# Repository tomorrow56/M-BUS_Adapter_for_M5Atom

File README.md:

# M-BUS_Adapter_for_M5Atom

### Support Page
https://thousandiy.wordpress.com/2020/05/22/m5atom-to-m-bus-adapter/

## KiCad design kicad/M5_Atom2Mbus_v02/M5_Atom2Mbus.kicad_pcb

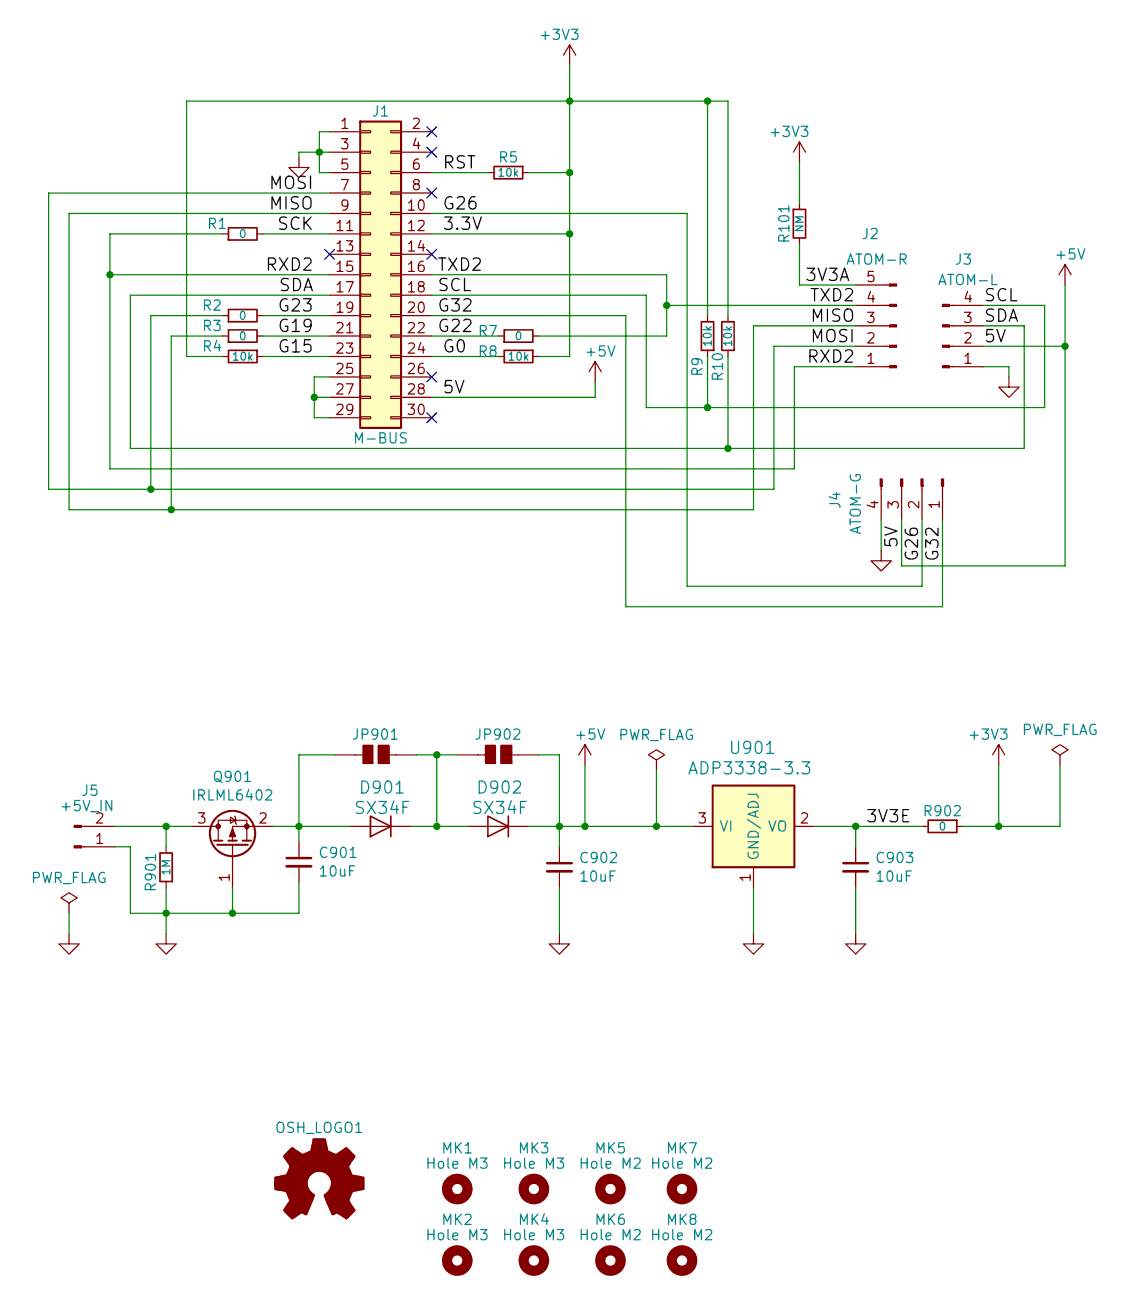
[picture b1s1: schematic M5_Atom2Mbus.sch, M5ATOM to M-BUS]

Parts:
C901, C902, C903: 10uF; C_0603_1608Metric
D901, D902: SX34F; D_SMA
J1: M-BUS; Pin_Header_MBUS_SMD_TH
J2: ATOM-R; PinHeader_1x05_P2.54mm_Vertical
J3: ATOM-L; PinHeader_1x04_P2.54mm_Vertical
J4: ATOM-G; Grove_4x2.00mm_Angle
J5: +5V_IN; PinHeader_1x02_P2.54mm_Horizontal
JP901, JP902: SOLDERJUMPER; SOLDERJUMPER_REFLOW
MK1, MK2, MK3, MK4: Hole M3; MountingHole_M3_mod
MK5, MK6, MK7, MK8: Hole M2; MountingHole_M2_mod
OSH_LOGO1: Logo_Open_Hardware_Small; OSHW-logo_silkscreen-front_4mm
Q901: IRLML6402; SOT-23
R1, R2, R3, R7, R902: 0; R_0603_1608Metric
R4, R5, R8, R9, R10: 10k; R_0603_1608Metric
R101: NM; R_0603_1608Metric
R901: 1M; R_0603_1608Metric
U901: ADP3338-3.3; SOT-223-3_TabPin2

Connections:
+3V3: J1.12, R4.2, R5.1, R8.1, R9.2, R10.2, R101.1, R902.1
+5V: C902.1, D902.1 (K), J1.28, J3.2, J4.3, JP902.1, U901.3 (VI)
/3V3A: J2.5, R101.2
/3V3E: C903.1, R902.2, U901.2 (VO)
/G0: J1.24, R8.2
/G15: J1.23, R4.1
/G19: J1.21, R3.2
/G22: J1.22, R7.1
/G23: J1.19, R2.2
/G26: J1.10, J4.2
/G32: J1.20, J4.1
/MISO: J1.9, J2.3, R3.1
/MOSI: J1.7, J2.2, R2.1
/RST: J1.6, R5.2
/RXD2: J1.15, J2.1, R1.1
/SCK: J1.11, R1.2
/SCL: J1.18, J3.4, R9.1
/SDA: J1.17, J3.3, R10.1
/TXD2: J1.16, J2.4, R7.2
GND: C901.2, C902.2, C903.2, J1.1, J1.3, J1.5, J3.1, J4.4, J5.1, Q901.1 (G), R901.1, U901.1 (GND/ADJ)
unnamed: C901.1, D901.2 (A), JP901.2, Q901.2 (S)
unnamed: D901.1 (K), D902.2 (A), JP901.1, JP902.2
unnamed: J1.25, J1.27, J1.29
unnamed: J5.2, Q901.3 (D), R901.2

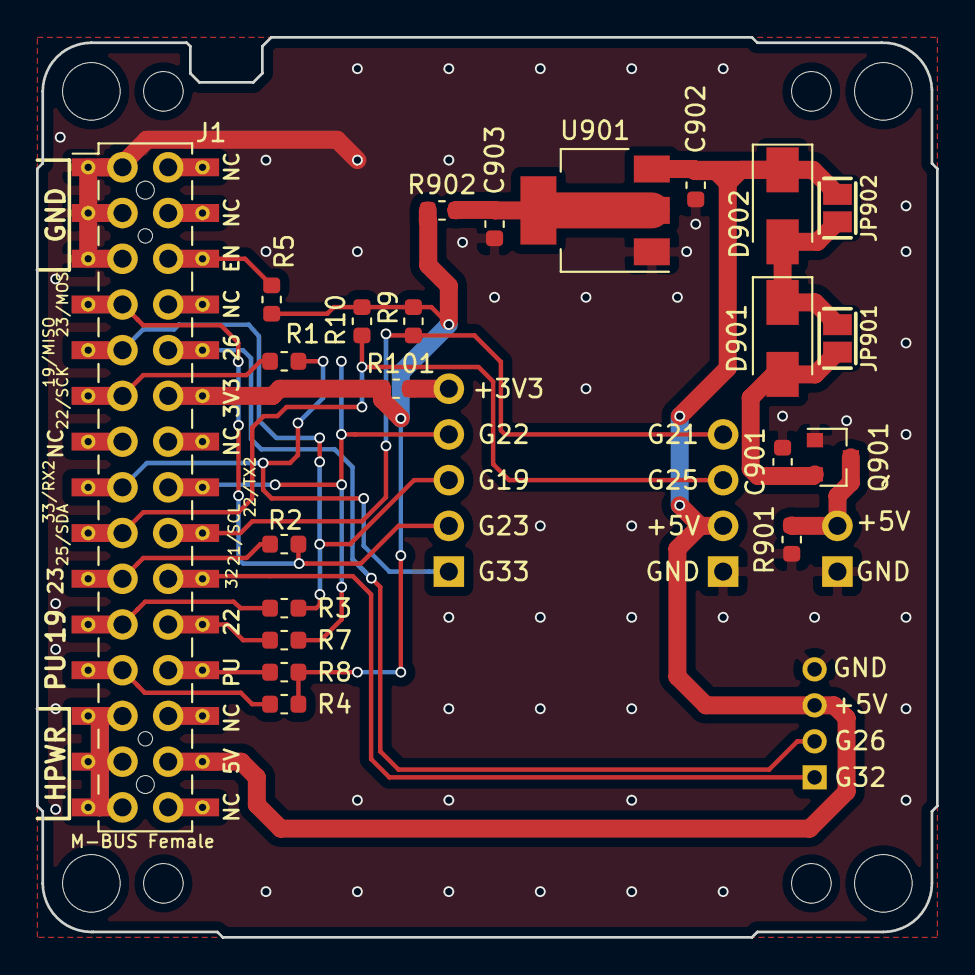
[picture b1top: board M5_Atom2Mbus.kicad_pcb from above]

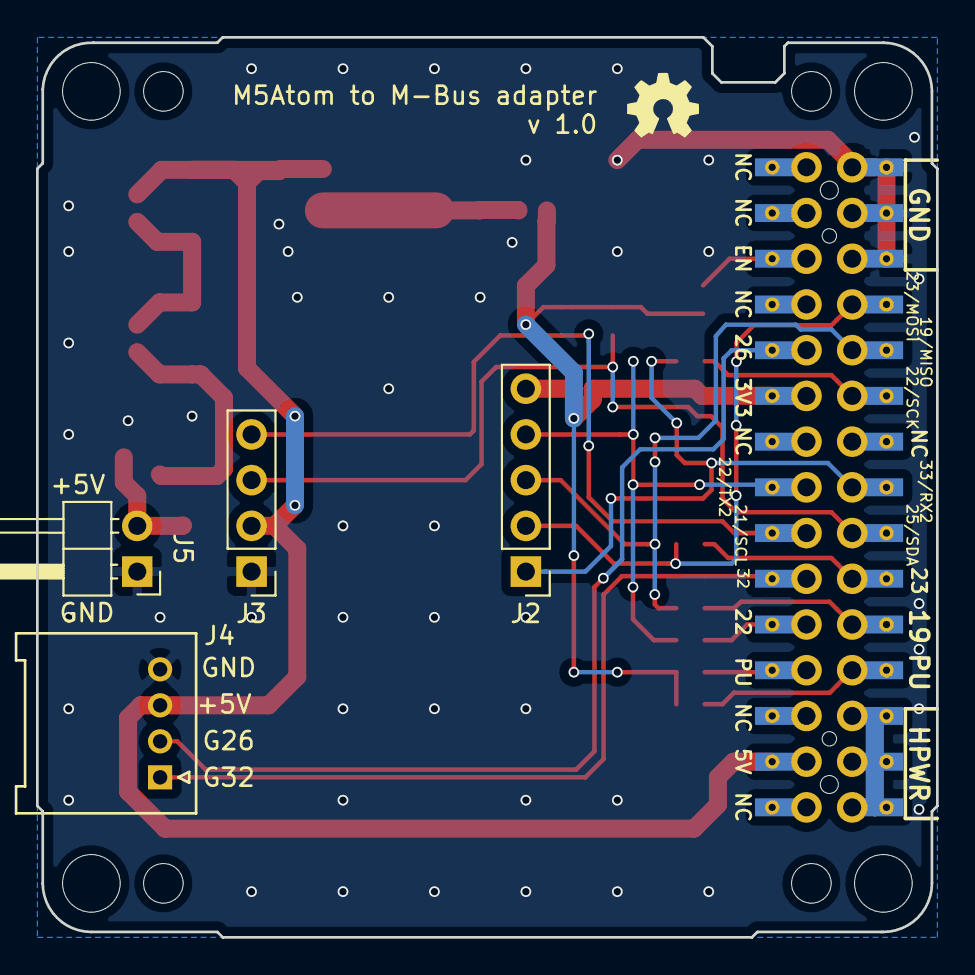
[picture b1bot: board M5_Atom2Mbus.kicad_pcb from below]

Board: 2 copper layers, 50.0 x 50.0 mm, 35 parts (5 on the bottom side), 24 nets.
